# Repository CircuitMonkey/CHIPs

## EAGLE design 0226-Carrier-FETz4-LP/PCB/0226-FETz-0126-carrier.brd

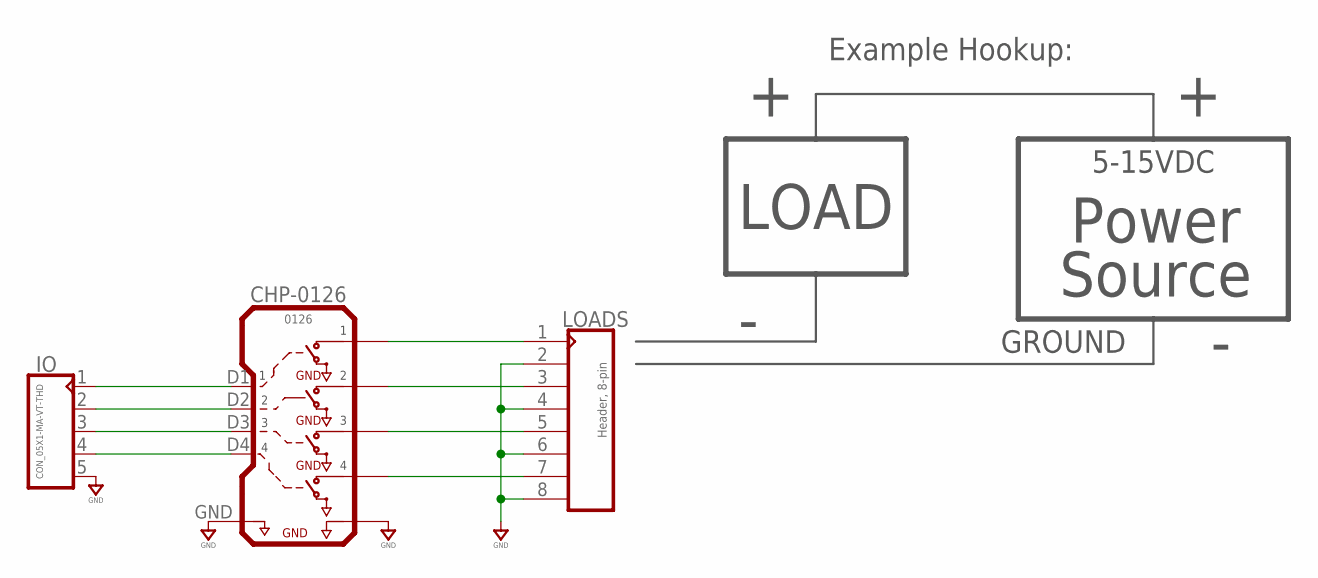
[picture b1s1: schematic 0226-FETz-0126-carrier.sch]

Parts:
CHP-0126: 0126; 0126A
IO: CON_05X1-MA-VT-THD; MA05X1-VT-THD
LOADS: Header, 8-pin; MA08X1-VT-THD

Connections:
GND: CHP-0126.GND, CHP-0126.GNDL (GND2), IO.5, LOADS.2, LOADS.4, LOADS.6, LOADS.8
unnamed: CHP-0126.D1 (1), IO.1
unnamed: CHP-0126.D2 (2), IO.2
unnamed: CHP-0126.D3 (3), IO.3
unnamed: CHP-0126.D4 (4), IO.4
unnamed: CHP-0126.L1, LOADS.1
unnamed: CHP-0126.L2, LOADS.3
unnamed: CHP-0126.L3, LOADS.5
unnamed: CHP-0126.L4, LOADS.7

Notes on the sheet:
LOAD
Power Source
Example Hookup:
5-15VDC
GROUND

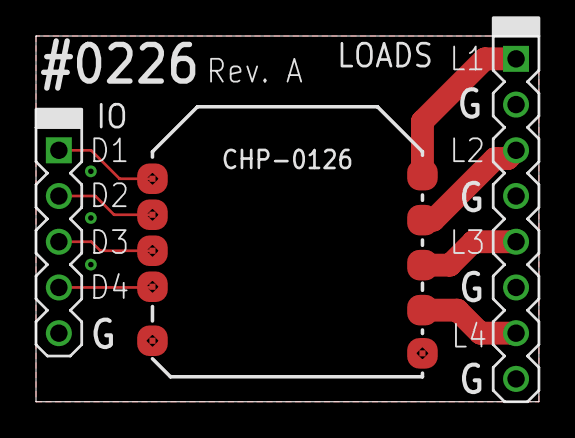
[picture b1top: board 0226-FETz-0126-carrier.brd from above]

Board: 2 copper layers, 27.9 x 20.3 mm, 3 parts (0 on the bottom side), 9 nets.

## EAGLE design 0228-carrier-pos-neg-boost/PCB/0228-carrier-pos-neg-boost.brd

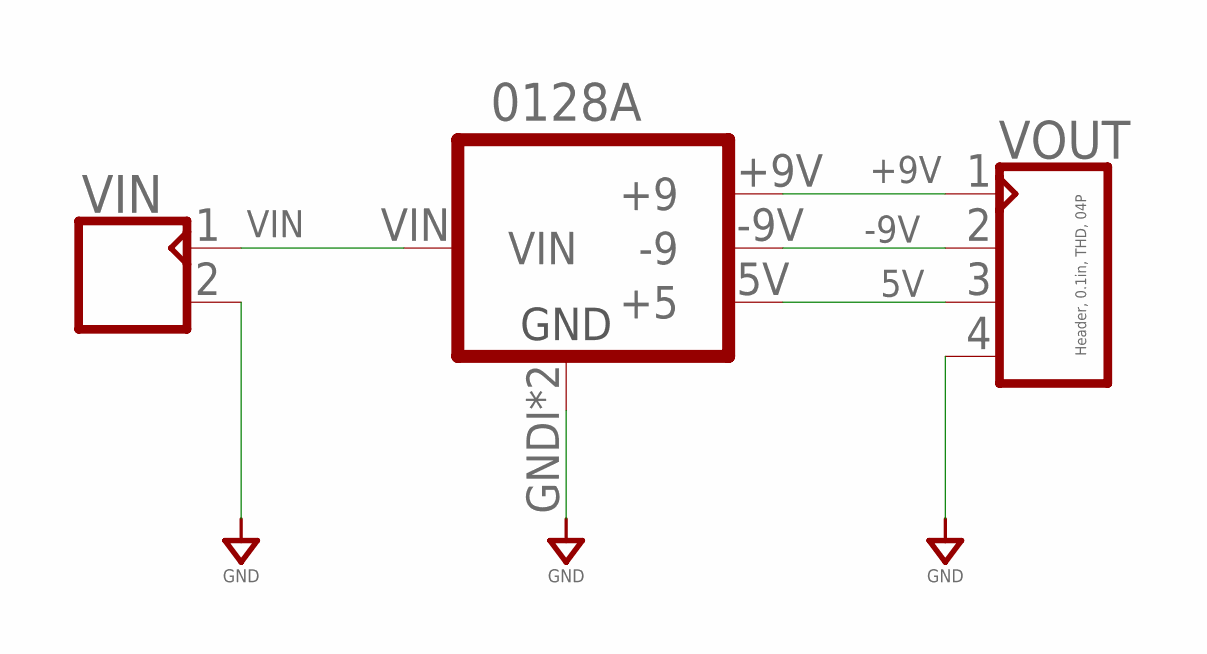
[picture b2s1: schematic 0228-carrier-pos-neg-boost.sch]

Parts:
0128A: 0128REV-A; 1028A
VIN: CON_02X1-2.54MM-THD-VT; MA02X1-VT-THD
VOUT: Header, 0.1in, THD, 04P; MA04X1-VT-THD

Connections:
5V: 0128A.5V (+5), VOUT.3
+9V: 0128A.+9V (+9), VOUT.1
-9V: 0128A.-9V (-9), VOUT.2
GND: 0128A.GNDI (GND), 0128A.GNDO (GND), VIN.2, VOUT.4
VIN: 0128A.VIN, VIN.1

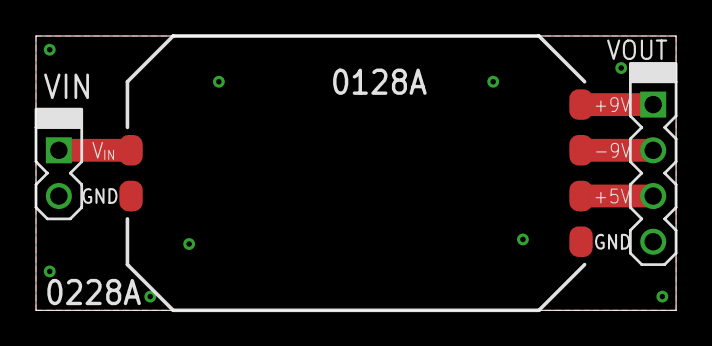
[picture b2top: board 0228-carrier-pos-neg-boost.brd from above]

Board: 2 copper layers, 35.6 x 15.2 mm, 3 parts (0 on the bottom side), 5 nets.

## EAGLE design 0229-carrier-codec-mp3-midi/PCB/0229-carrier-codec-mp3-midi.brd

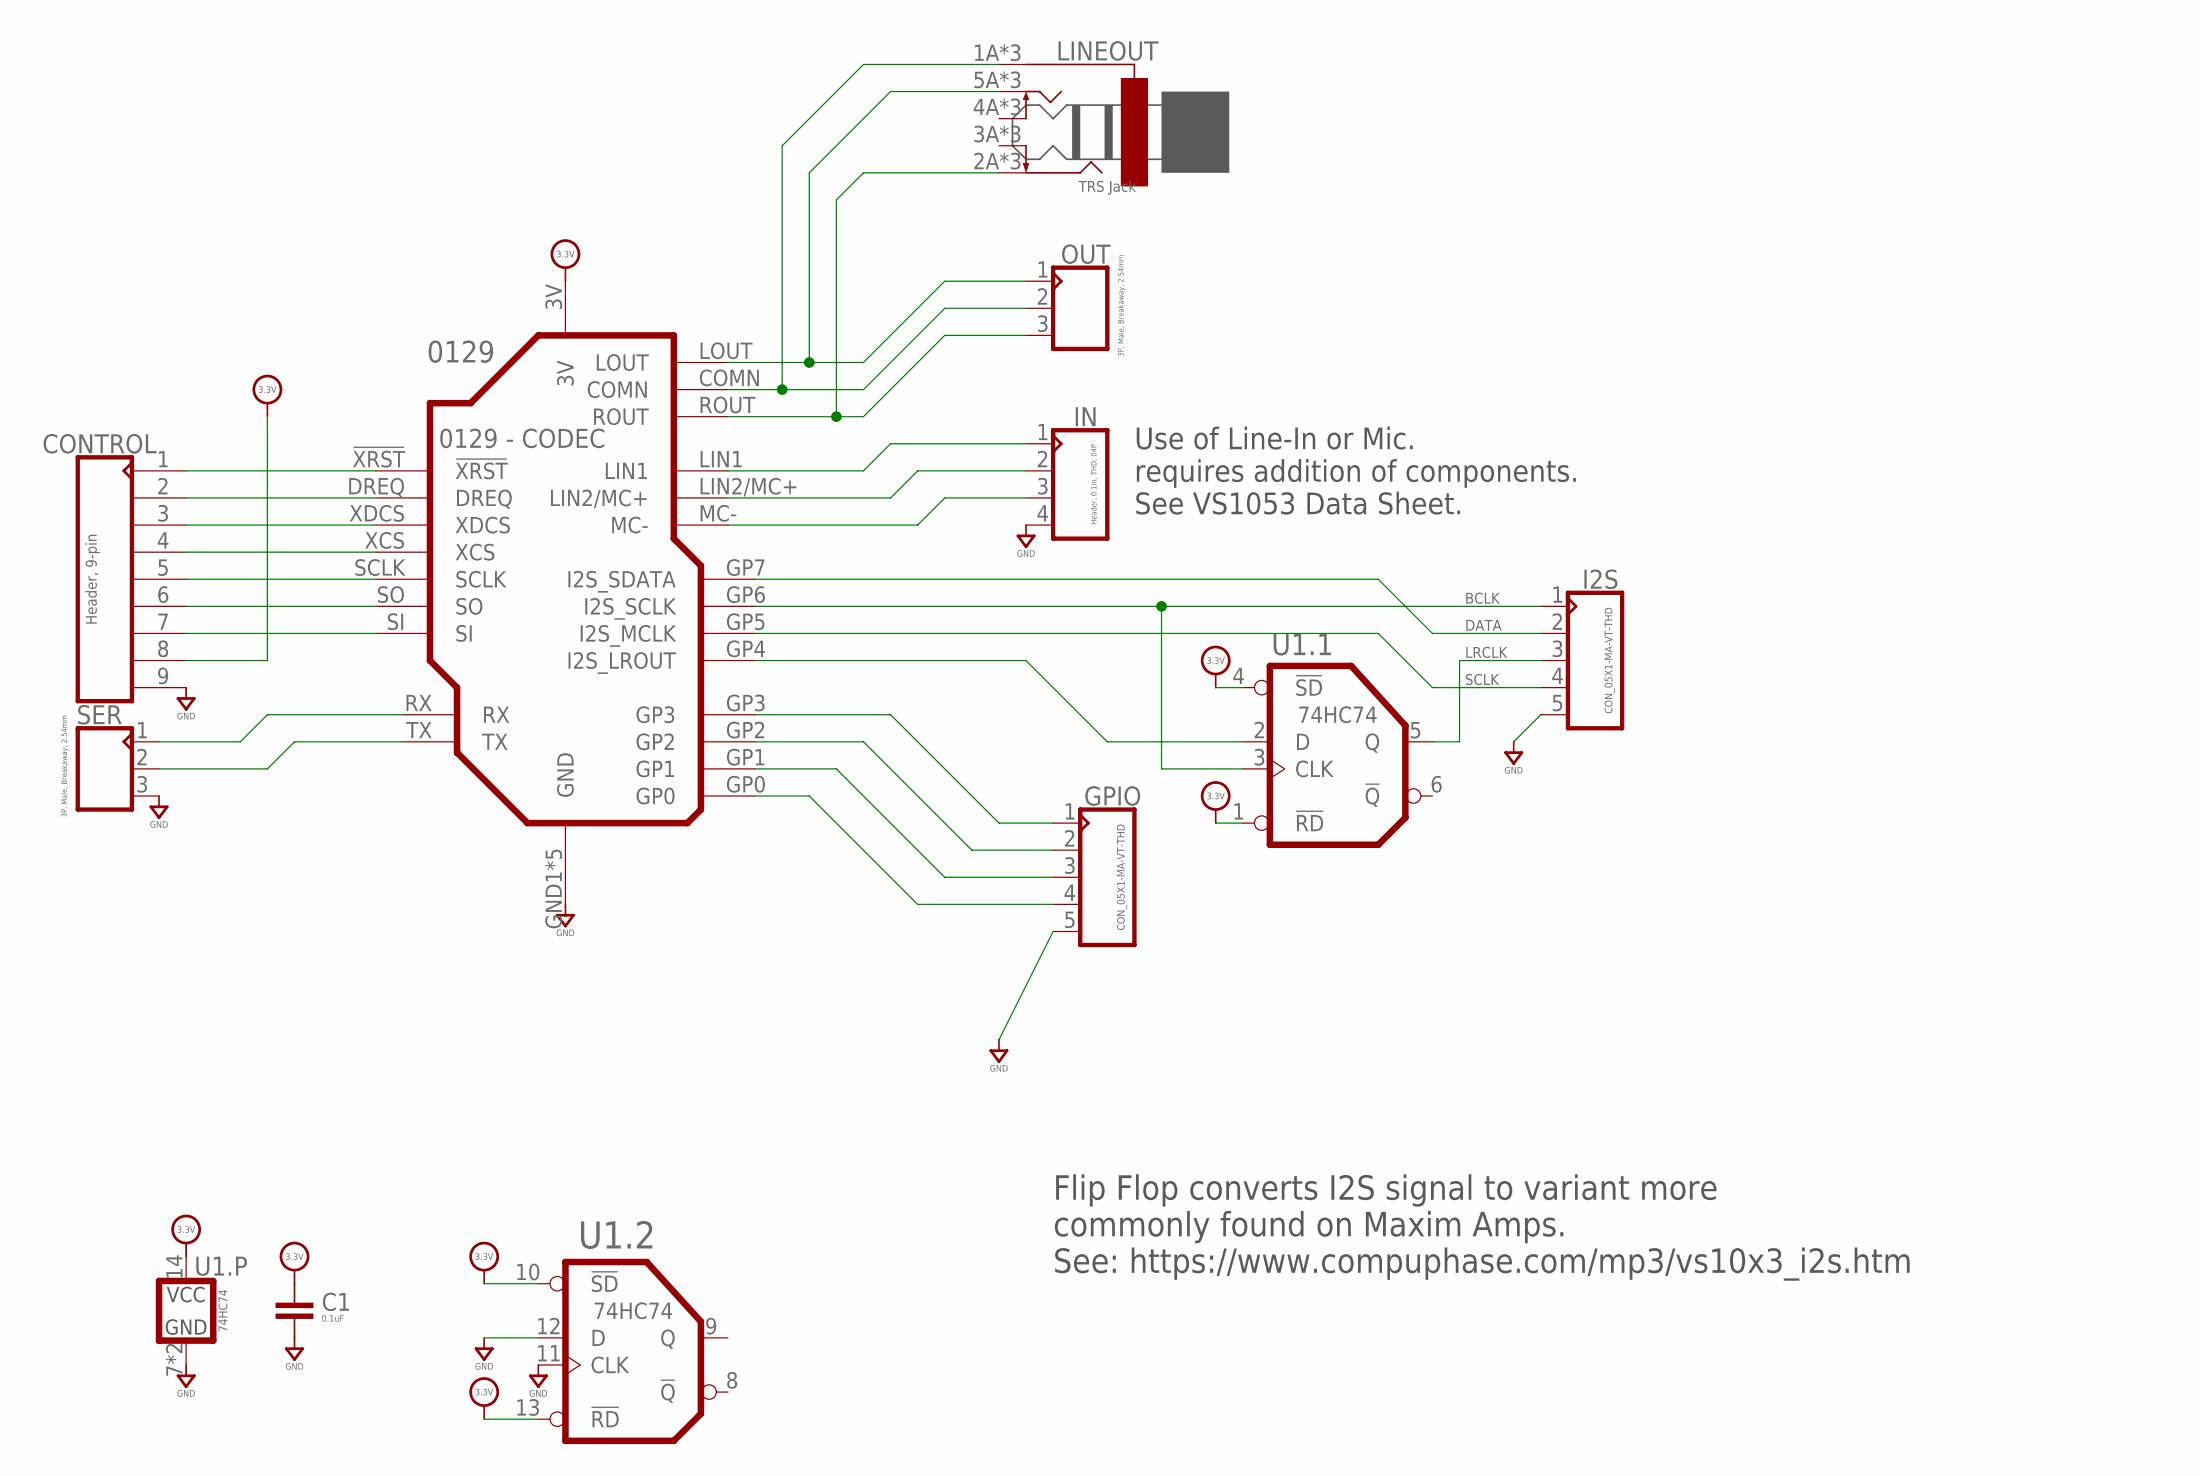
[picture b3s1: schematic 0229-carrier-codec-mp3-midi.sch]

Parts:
0129: 0129 - CODEC; 0129A
C1: 0.1uF; 0603-CAP
CONTROL: Header, 9-pin; MA09X1-VT-THD
GPIO: CON_05X1-MA-VT-THD; MA05X1-VT-THD
I2S: CON_05X1-MA-VT-THD; MA05X1-VT-THD
IN: Header, 0.1in, THD, 04P; MA04X1-VT-THD
LINEOUT: TRS Jack; PJ-324
OUT: 3P, Male, Breakaway, 2.54mm; MA03X1-VT-THD
SER: 3P, Male, Breakaway, 2.54mm; MA03X1-VT-THD
U1: 74HC74; QFN14

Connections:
+3.3V: 0129.3V, C1.1, CONTROL.8, U1.1 (!RD), U1.4 (!SD), U1.10 (!SD), U1.13 (!RD), U1.14 (VCC)
BCLK: 0129.GP6 (I2S_SCLK), I2S.1, U1.3 (CLK)
DATA: 0129.GP7 (I2S_SDATA), I2S.2
GND: 0129.GND1 (GND), 0129.GND2 (GND), 0129.GND3 (GND), 0129.GND4 (GND), 0129.GND5 (GND), C1.2, CONTROL.9, GPIO.5, I2S.5, IN.4, SER.3, U1.7 (GND), U1.11 (CLK), U1.12 (D), U1.PAD (GND)
LRCLK: I2S.3, U1.5 (Q)
unnamed: 0129.COMN, LINEOUT.1A (S), LINEOUT.1A1 (S), LINEOUT.1A2 (S), OUT.2
unnamed: 0129.GP4 (I2S_LROUT), U1.2 (D)
unnamed: 0129.LOUT, LINEOUT.5A (T), LINEOUT.5A1 (T), LINEOUT.5A2 (T), OUT.1
unnamed: 0129.MC-, IN.3
unnamed: 0129.LIN2/MC+, IN.2
unnamed: 0129.LIN1, IN.1
unnamed: 0129.GP3, GPIO.1
unnamed: 0129.GP2, GPIO.2
unnamed: 0129.GP1, GPIO.3
unnamed: 0129.GP0, GPIO.4
unnamed: 0129.!XRST, CONTROL.1
unnamed: 0129.DREQ, CONTROL.2
unnamed: 0129.XDCS, CONTROL.3
unnamed: 0129.XCS, CONTROL.4
unnamed: 0129.SCLK, CONTROL.5
unnamed: 0129.SO, CONTROL.6
unnamed: 0129.SI, CONTROL.7
unnamed: 0129.RX, SER.1
unnamed: 0129.TX, SER.2
unnamed: 0129.ROUT, LINEOUT.2A (R), LINEOUT.2A1 (R), LINEOUT.2A2 (R), OUT.3
SCLK: 0129.GP5 (I2S_MCLK), I2S.4

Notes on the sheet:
Use of Line-In or Mic. requires addition of components. See VS1053 Data Sheet.
Flip Flop converts I2S signal to variant more commonly found on Maxim Amps. See: https://www.compuphase.com/mp3/vs10x3_i2s.htm

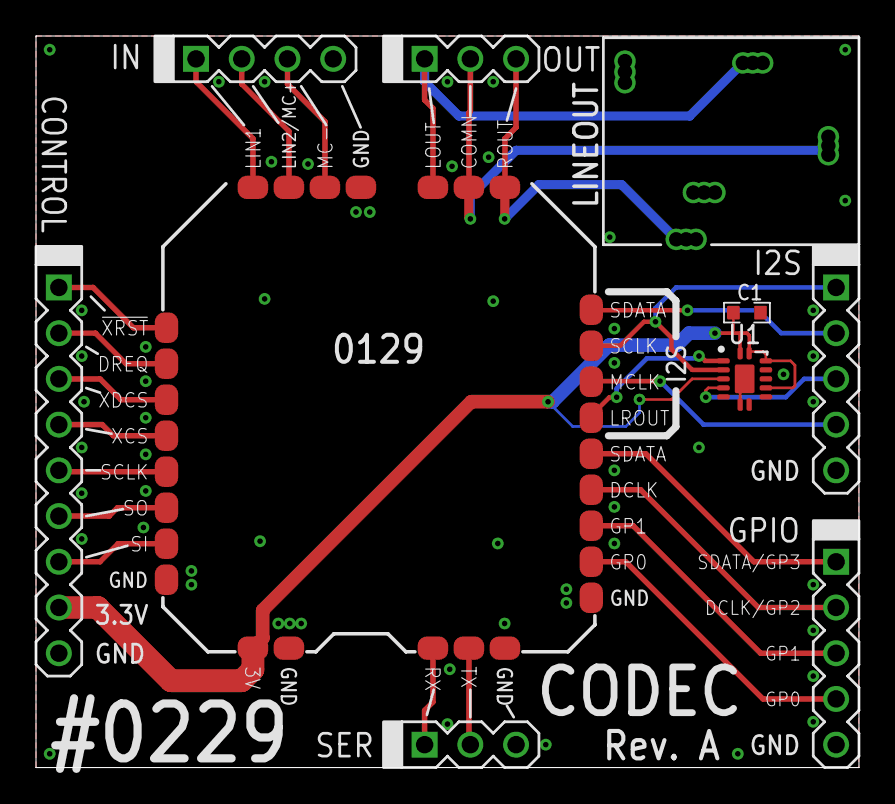
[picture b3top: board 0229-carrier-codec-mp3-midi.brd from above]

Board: 2 copper layers, 45.7 x 40.6 mm, 10 parts (0 on the bottom side), 26 nets.

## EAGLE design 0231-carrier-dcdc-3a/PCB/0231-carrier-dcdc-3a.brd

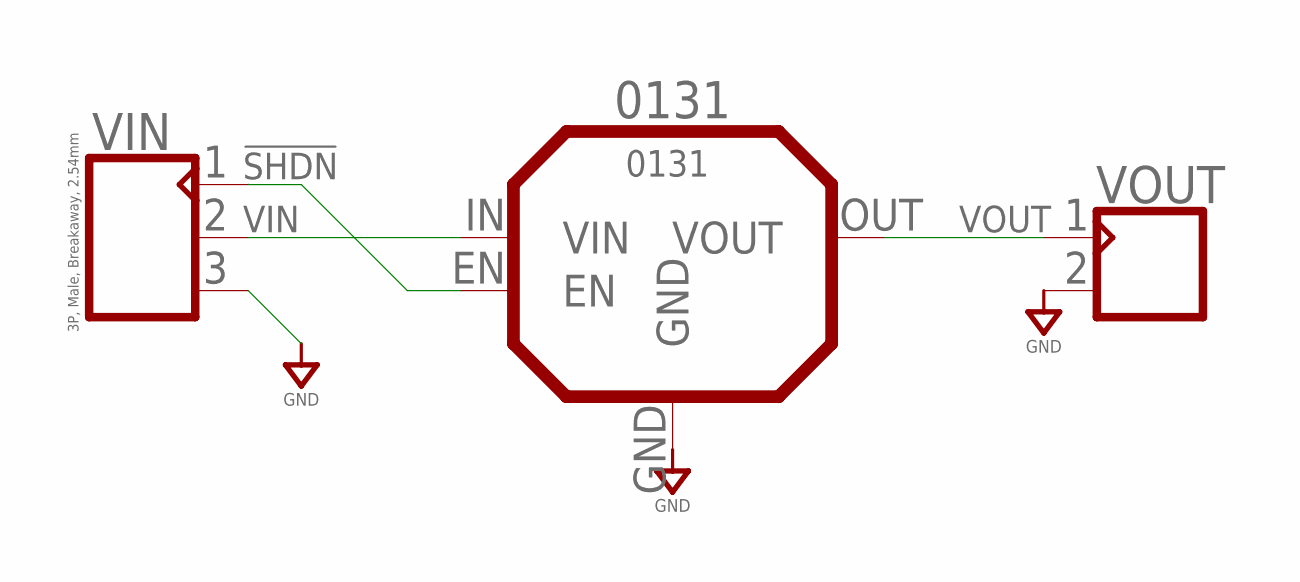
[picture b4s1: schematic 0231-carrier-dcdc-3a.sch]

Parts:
0131: 0131; 0131A
VIN: 3P, Male, Breakaway, 2.54mm; MA03X1-VT-THD
VOUT: CON_02X1-2.54MM-THD-VT; MA02X1-VT-THD

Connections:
!SHDN: 0131.EN, VIN.1
GND: 0131.GND, VIN.3, VOUT.2
VIN: 0131.IN (VIN), VIN.2
VOUT: 0131.OUT (VOUT), VOUT.1

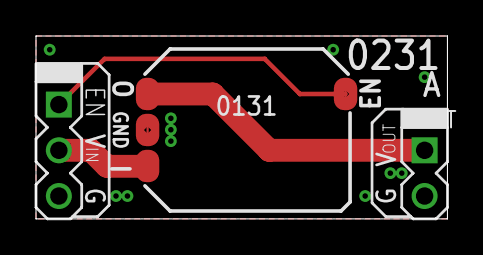
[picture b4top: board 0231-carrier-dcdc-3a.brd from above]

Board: 2 copper layers, 22.9 x 10.2 mm, 3 parts (0 on the bottom side), 4 nets.

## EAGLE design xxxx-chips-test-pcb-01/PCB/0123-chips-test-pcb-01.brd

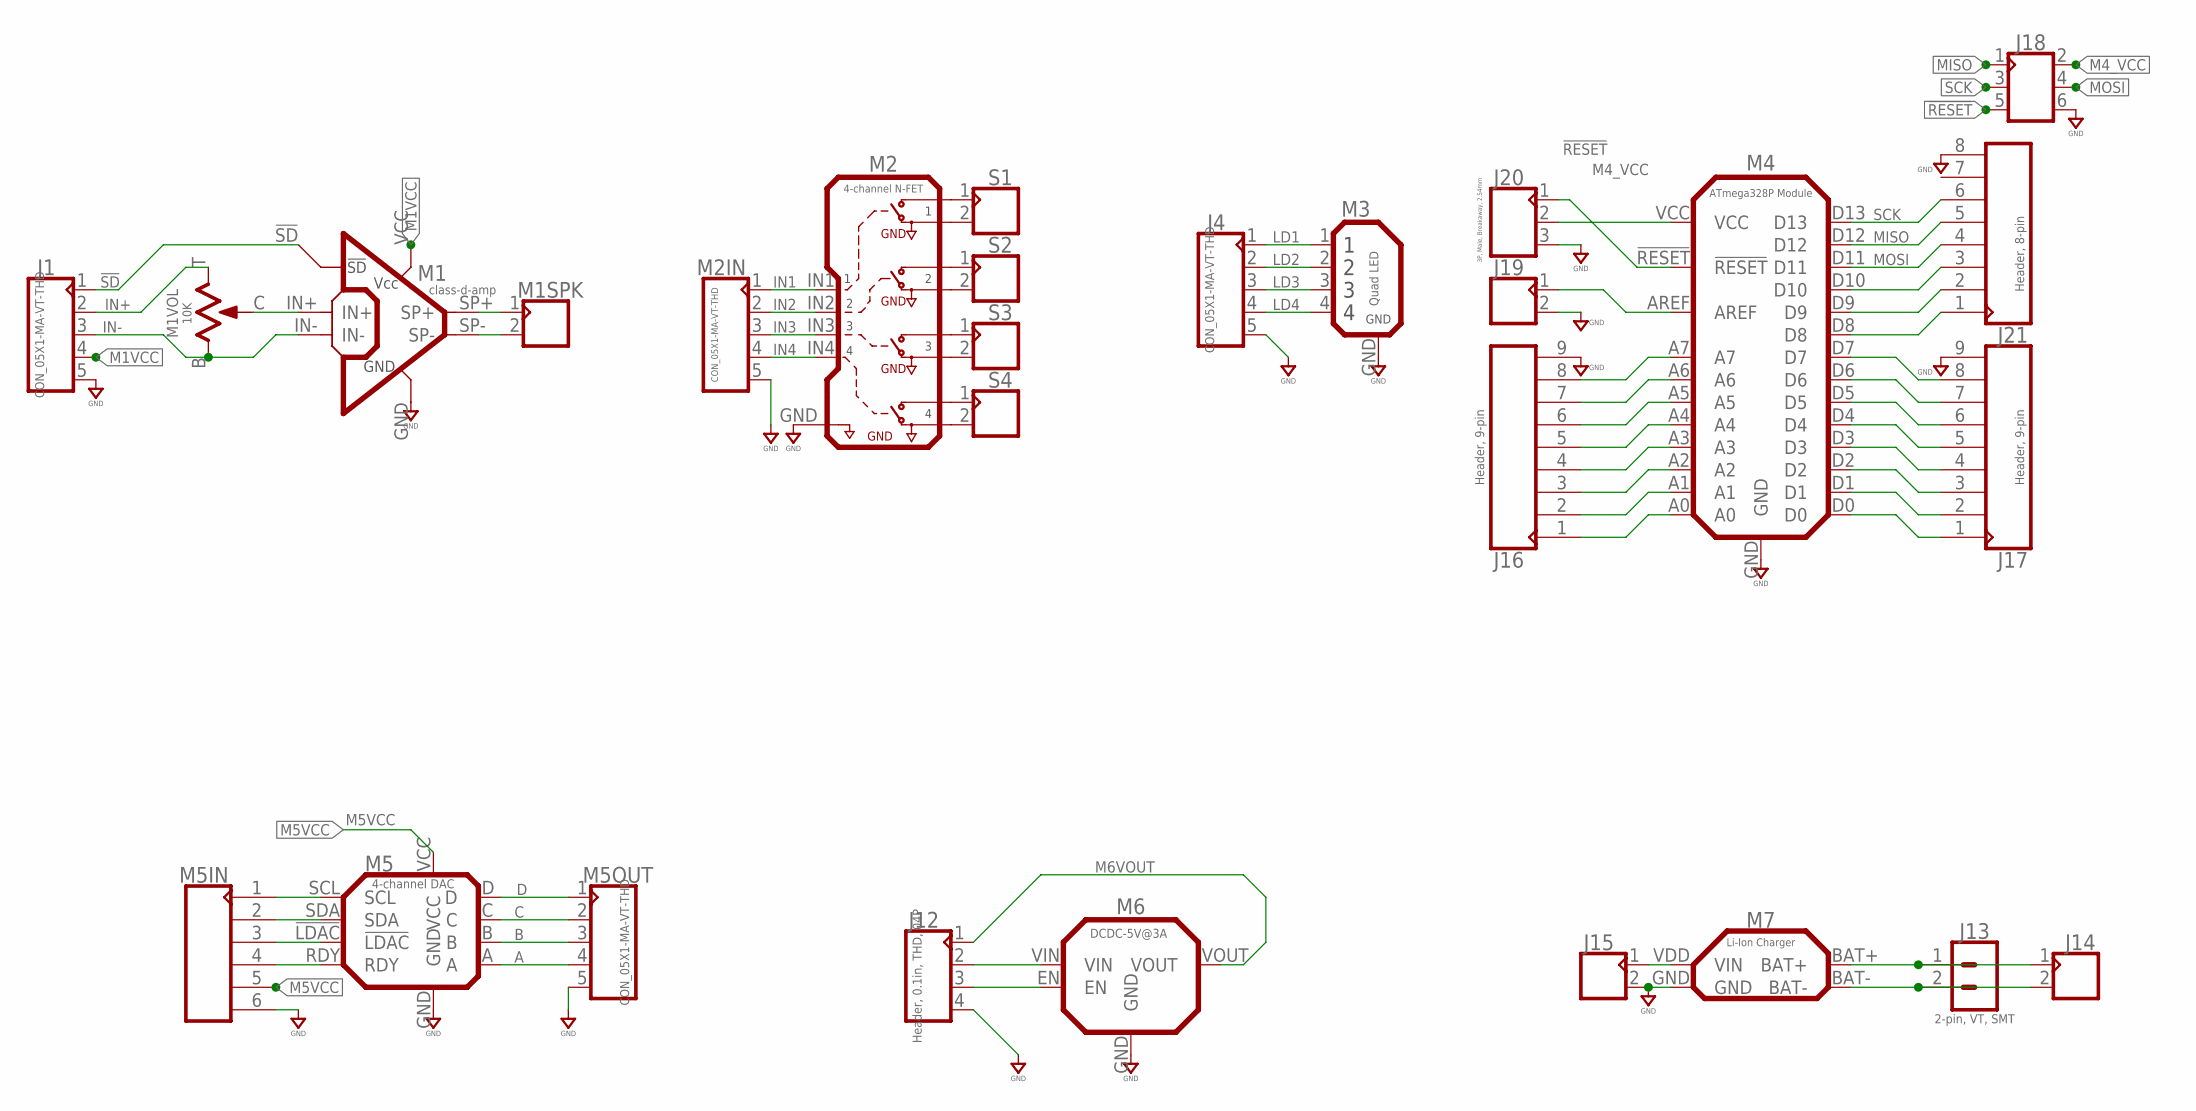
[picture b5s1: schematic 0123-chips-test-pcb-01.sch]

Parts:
J1, J4: CON_05X1-MA-VT-THD; MA05X1-VT-THD
J12: Header, 0.1in, THD, 04P; MA04X1-VT-THD
J13: 2-pin, VT, SMT; B2B-PH-SM4
J14, J15, J19: CON_02X1-2.54MM-THD-VT; MA02X1-VT-THD
J16, J17: Header, 9-pin; MA09X1-VT-THD
J18: CON_03X2-VT; MA03X2-VT-THD
J20: 3P, Male, Breakaway, 2.54mm; MA03X1-VT-THD
J21: Header, 8-pin; MA08X1-VT-THD
M1: class-d-amp; 0116A
M1SPK: CON_02X1-2.54MM-THD-VT; MA02X1-VT-THD
M1VOL: 10K; TRIM_BOURNS_TC33X
M2: 4-channel N-FET; 0117A
M2IN, M5OUT: CON_05X1-MA-VT-THD; MA05X1-VT-THD
M3: Quad LED; 0118A
M4: ATmega328P Module; 0119A
M5: 4-channel DAC; 0120A
M5IN: CON_06X1-VT; MA06X1-VT-THD
M6: DCDC-5V@3A; 0121A
M7: Li-Ion Charger; 0122A
S1, S2, S3, S4: CON_02X1-2.54MM-THD-VT; MA02X1-VT-THD

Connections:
!RESET: J18.5, J20.1, M4.!RESET
!SD: J1.1, M1.!SD
A: M5.A, M5OUT.4
B: M5.B, M5OUT.3
C: M5.C, M5OUT.2
D: M5.D, M5OUT.1
GND: J1.5, J4.5, J12.4, J15.2, J16.9, J17.9, J18.6, J19.2, J20.3, J21.8, M1.GND, M2.GND, M2IN.5, M3.GND, M4.GND, M5.GND, M5IN.6, M5OUT.5, M6.GND, M7.GND
IN1: M2.IN1 (1), M2IN.1
IN2: M2.IN2 (2), M2IN.2
IN3: M2.IN3 (3), M2IN.3
IN4: M2.IN4 (4), M2IN.4
IN+: J1.2, M1VOL.T (3)
IN-: J1.3, M1.IN-, M1VOL.B (1)
LD1: J4.1, M3.1
LD2: J4.2, M3.2
LD3: J4.3, M3.3
LD4: J4.4, M3.4
M1VCC: J1.4, M1.VCC
M4_VCC: J18.2, J20.2, M4.VCC
M5VCC: M5.VCC, M5IN.5
M6VOUT: J12.1, M6.VOUT
MISO: J18.1, J21.5, M4.D12
MOSI: J18.4, J21.4, M4.D11
unnamed: M1.SP-, M1SPK.2
unnamed: M1.SP+, M1SPK.1
unnamed: M5.RDY, M5IN.4
unnamed: M5.!LDAC, M5IN.3
unnamed: M5.SDA, M5IN.2
unnamed: M5.SCL, M5IN.1
unnamed: M2.GND1, S1.2
unnamed: M2.OUT1 (V1), S1.1
unnamed: M2.GND2, S2.2
unnamed: M2.OUT2 (V2), S2.1
unnamed: M2.GND3, S3.2
unnamed: M2.OUT3 (V3), S3.1
unnamed: M2.GND4, S4.2
unnamed: M2.OUT4 (V4), S4.1
unnamed: J12.2, M6.VIN
unnamed: J12.3, M6.EN
unnamed: J13.1, J14.1, M7.BAT+
unnamed: J13.2, J14.2, M7.BAT-
unnamed: J17.1, M4.D0
unnamed: J15.1, M7.VDD (VIN)
unnamed: J17.2, M4.D1
unnamed: J17.3, M4.D2
unnamed: J17.4, M4.D3
unnamed: J17.5, M4.D4
unnamed: J17.6, M4.D5
unnamed: J17.7, M4.D6
unnamed: J17.8, M4.D7
unnamed: J16.1, M4.A0
unnamed: J16.2, M4.A1
unnamed: J16.3, M4.A2
unnamed: J16.4, M4.A3
unnamed: J16.5, M4.A4
unnamed: J16.6, M4.A5
unnamed: J16.7, M4.A6
unnamed: J16.8, M4.A7
unnamed: J19.1, M4.AREF
unnamed: M1.IN+, M1VOL.C (2)
unnamed: J21.1, M4.D8
unnamed: J21.2, M4.D9
unnamed: J21.3, M4.D10
SCK: J18.3, J21.6, M4.D13

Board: 2 copper layers, 28 parts (0 on the bottom side), 64 nets, no tracks yet.
